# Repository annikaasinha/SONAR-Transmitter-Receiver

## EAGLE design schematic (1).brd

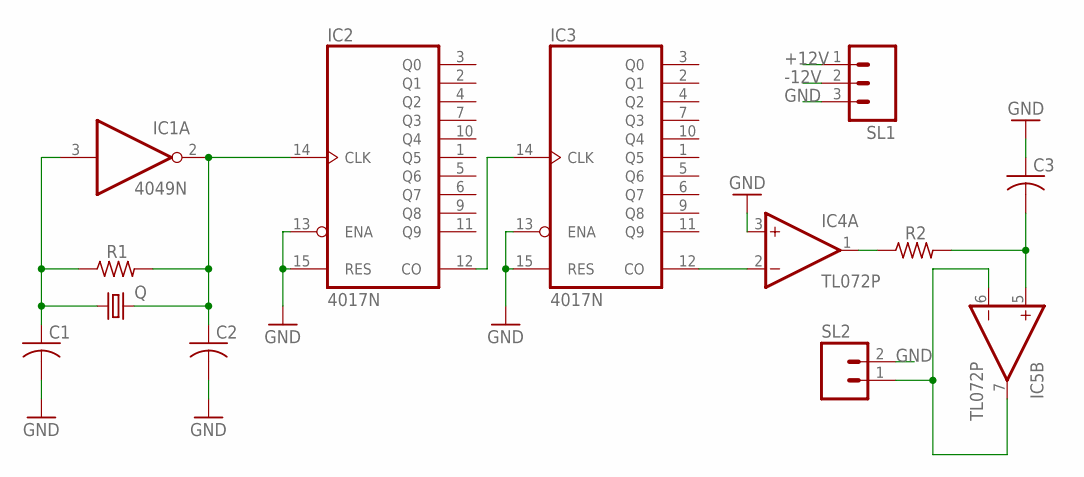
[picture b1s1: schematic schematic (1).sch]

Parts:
C1, C2, C3: C-US025-024X044; C025-024X044
IC1: 4049N; DIL16
IC2, IC3: 4017N; DIL16
IC4, IC5: TL072P; DIL08
Q: CRYSTALHC49S; HC49/S
R1, R2: R-US_0204/7; 0204/7
SL1: M03; 03P
SL2: M02; 02P

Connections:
+12V: IC1.1 (VDD), IC2.16 (VDD), IC3.16 (VDD), IC4.8 (V+), IC5.8 (V+), SL1.1
-12V: IC4.4 (V-), IC5.4 (V-), SL1.2
GND: C1.2, C2.2, C3.1, IC1.8 (VSS), IC2.8 (VSS), IC2.13 (ENA), IC2.15 (RES), IC3.8 (VSS), IC3.13 (ENA), IC3.15 (RES), IC4.3 (+IN), SL1.3, SL2.2
unnamed: C1.1, IC1.3 (I), Q.1, R1.1
unnamed: C2.1, IC1.2 (O), IC2.14 (CLK), Q.2, R1.2
unnamed: IC2.12 (CO), IC3.14 (CLK)
unnamed: IC3.12 (CO), IC4.2 (-IN)
unnamed: IC4.1 (OUT), R2.1
unnamed: C3.2, IC5.5 (+IN), R2.2
unnamed: IC5.6 (-IN), IC5.7 (OUT), SL2.1

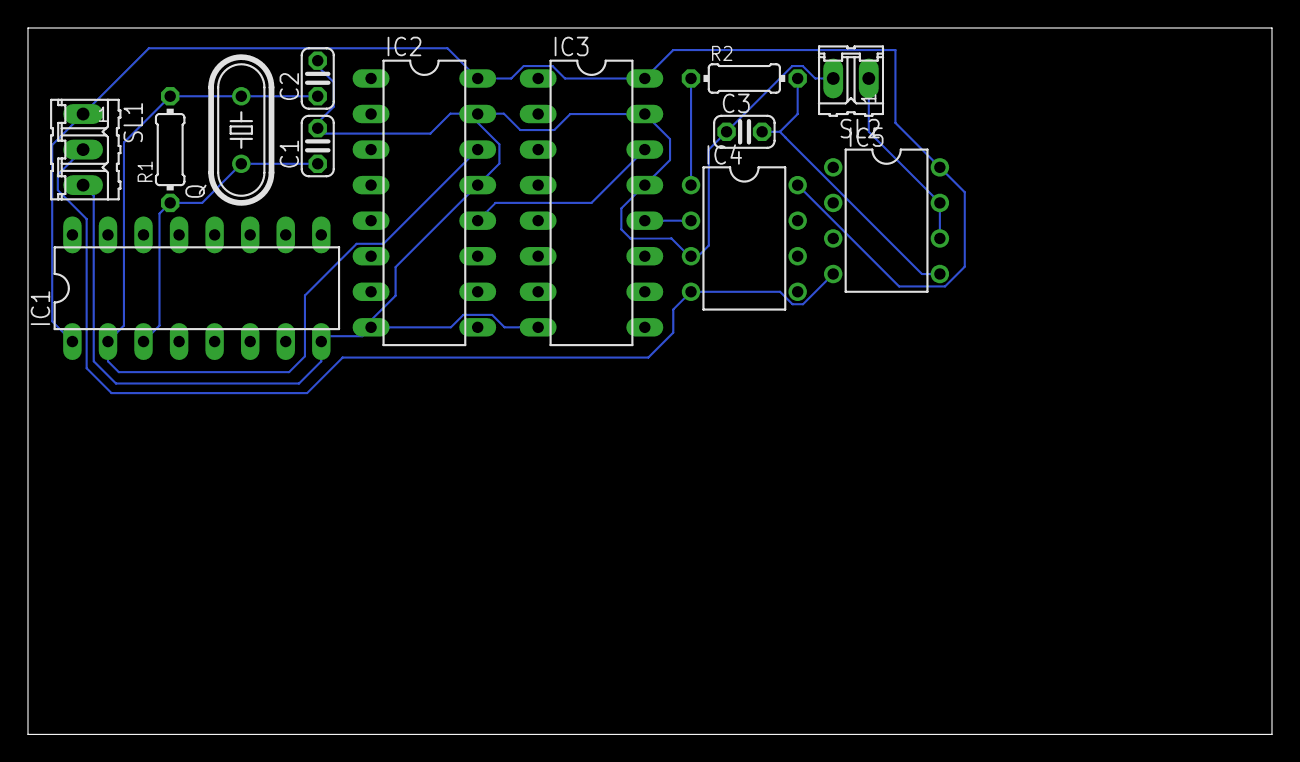
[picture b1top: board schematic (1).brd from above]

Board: 2 copper layers, 88.9 x 50.5 mm, 13 parts (0 on the bottom side), 10 nets.
